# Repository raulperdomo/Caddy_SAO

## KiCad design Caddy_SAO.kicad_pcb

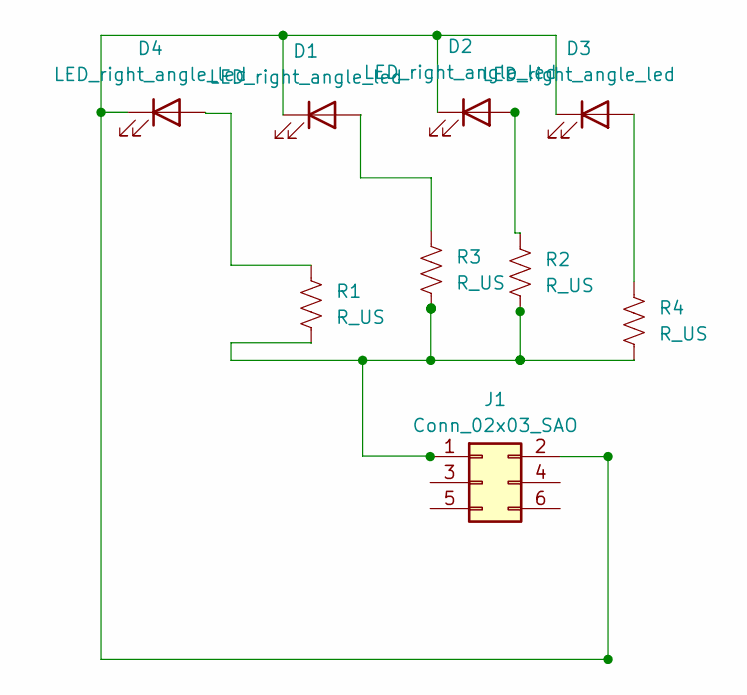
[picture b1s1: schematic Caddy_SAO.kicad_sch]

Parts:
D1, D2, D3, D4: LED_right_angle_led; 1206_right_angle_led
J1: Conn_02x03_SAO; Simple_Addon_v2-SAO-2x3
R1, R2, R3, R4: R_US; R_1206_3216Metric_Pad1.30x1.75mm_HandSolder

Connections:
unnamed: D1.2 (A), R3.1
unnamed: D1.1 (K), D2.1 (K), D3.1 (K), D4.1 (K), J1.2
unnamed: D2.2 (A), R2.1
unnamed: D3.2 (A), R4.1
unnamed: D4.2 (A), R1.1
unnamed: J1.1, R1.2, R2.2, R3.2, R4.2

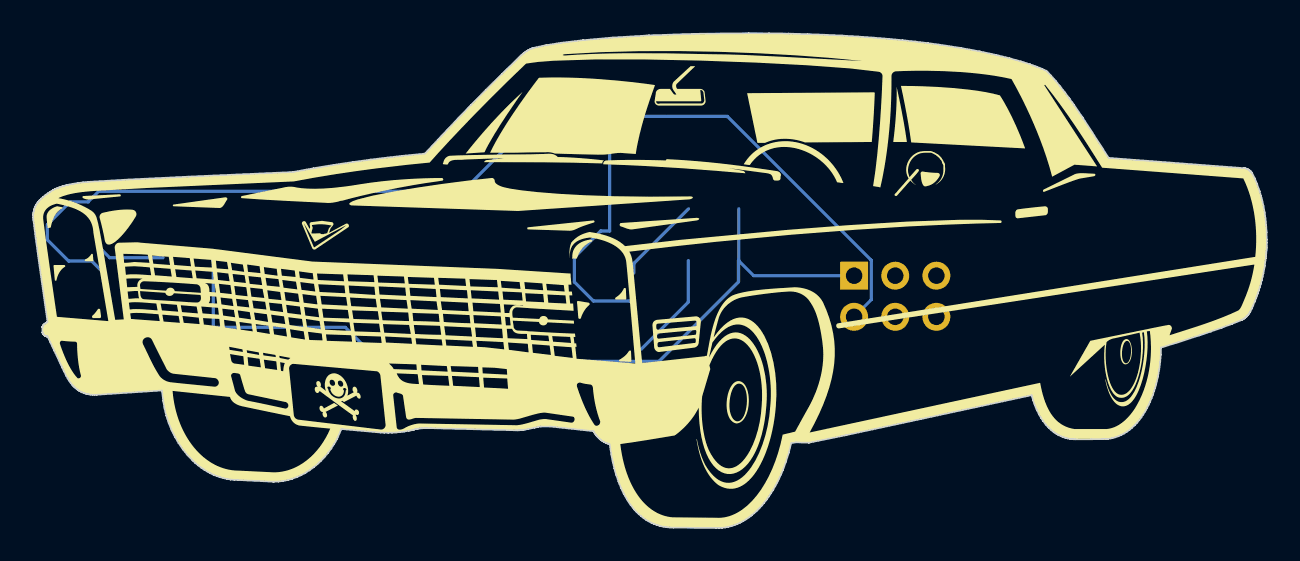
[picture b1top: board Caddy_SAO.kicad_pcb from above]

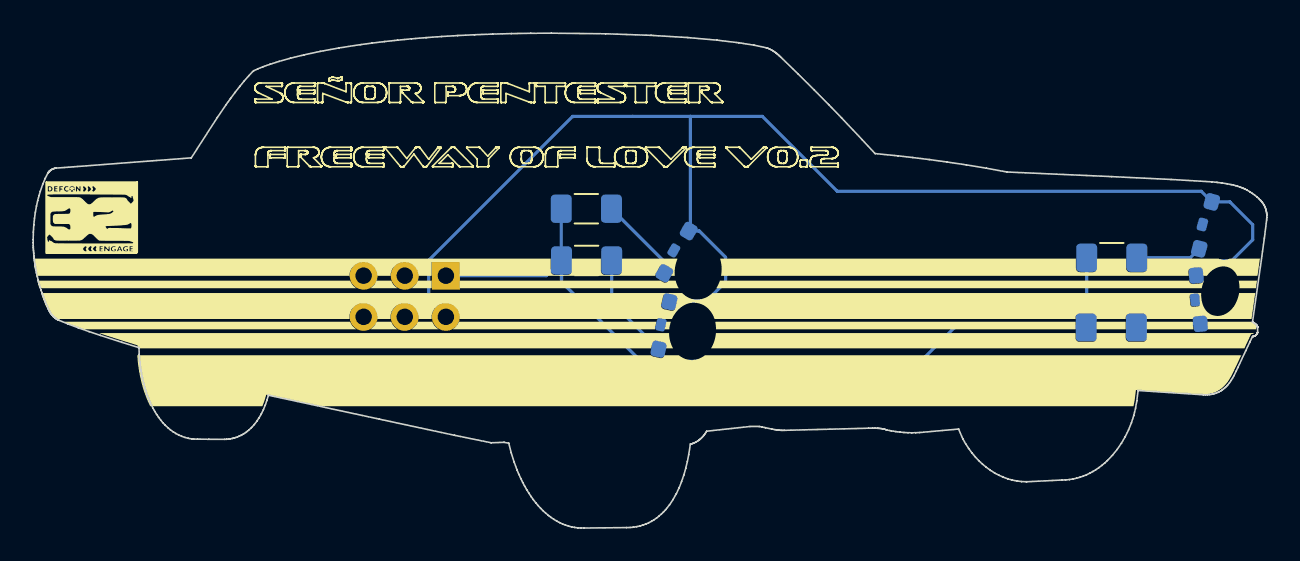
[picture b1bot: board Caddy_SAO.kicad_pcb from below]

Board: 2 copper layers, 76.2 x 30.6 mm, 9 parts (8 on the bottom side), 6 nets.

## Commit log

2025-02-28 Files
